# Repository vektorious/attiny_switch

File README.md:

# attiny_switch

Repository layout:
- `src/`: ATtiny1614 firmware (PlatformIO project)
- `pcb/`: KiCad project and gerbers

## Firmware target

- MCU: `ATtiny1614`
- `PA1`: ISP772T `IN` control
- `PA0`: dedicated `UPDI/RESET` pin, reserved for programming/debug and **not** used for switch control

Current behavior:
- On reset, drive `PA1` low immediately
- Then loop forever: OFF 50 min, ON 10 min
- MCU sleeps in `STANDBY` and wakes from RTC once per minute

## PlatformIO

`platformio.ini` is configured for bare-metal register-level C (no Arduino framework).

Build:

```powershell
pio run
```

Upload over UPDI (PA0):

1. Set your serial port in `platformio.ini` (`upload_port = COMx`).
2. Run:

```powershell
pio run -t upload
```

The configured upload command uses `avrdude` with `serialupdi`.

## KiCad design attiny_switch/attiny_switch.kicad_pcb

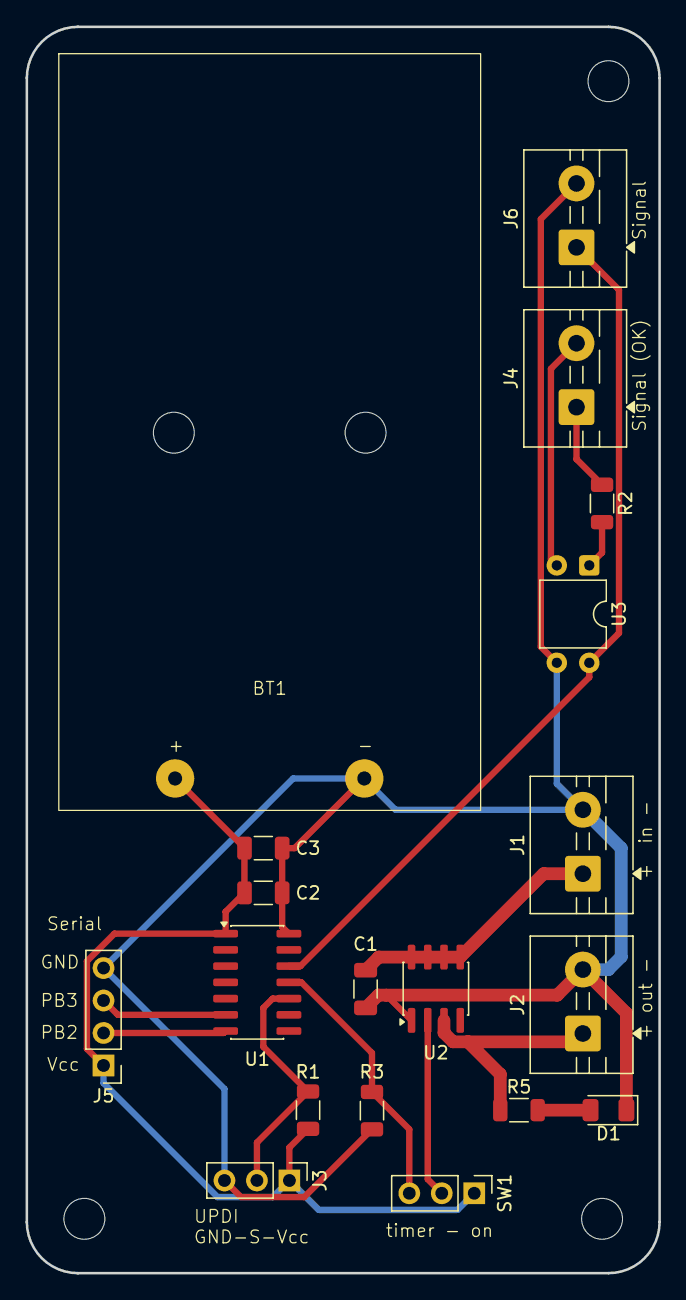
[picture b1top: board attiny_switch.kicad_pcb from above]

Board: 2 copper layers, 49.5 x 97.5 mm, 22 parts (0 on the bottom side), 14 nets.

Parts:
BT1: Battery_Cell; Untitled
C1, C2: 100nF; C_1206_3216Metric
C3: 10uF; C_1206_3216Metric
D1: LED; LED_1206_3216Metric
H1, H2, H3: MountingHole; MountingHole_3.2mm_M3
J1: 12V in; TerminalBlock_MaiXu_MX126-5.0-02P_1x02_P5.00mm
J2: 12V out; TerminalBlock_MaiXu_MX126-5.0-02P_1x02_P5.00mm
J3: UPDI Connector; PinHeader_1x03_P2.54mm_Vertical
J4: RPI Signal (OK); TerminalBlock_MaiXu_MX126-5.0-02P_1x02_P5.00mm
J5: Serial Connector; PinHeader_1x04_P2.54mm_Vertical
J6: RPI Signal; TerminalBlock_MaiXu_MX126-5.0-02P_1x02_P5.00mm
R1: 4,7k; R_1206_3216Metric
R2: 1k87; R_1206_3216Metric
R3: 100k; R_1206_3216Metric
R5: 7,5k; R_1206_3216Metric
SW1: SW_DPDT_x2; PinHeader_1x03_P2.54mm_Vertical
U1: ATtiny1614-SS; SOIC-14_3.9x8.7mm_P1.27mm
U2: ISP772T; SOIC-8_3.9x4.9mm_P1.27mm
U3: Optocoupler; DIP-4_W7.62mm

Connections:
GND: BT1.2 (-), C1.2, C2.1, C3.2, D1.1 (K), J1.2, J2.2, J3.3, J5.4, J6.2, R3.1, U1.14 (GND), U2.1 (GND), U3.3
unnamed: BT1.1 (+), C2.2, C3.1, J3.1, J5.1, R1.1, SW1.1 (A), U1.1 (VCC)
unnamed: D1.2 (A), R5.2
unnamed: C1.1, J1.1, U2.5 (VBB_1), U2.6 (VBB_2), U2.7 (VBB_3), U2.8 (VBB_4)
unnamed: J2.1, R5.1, U2.3 (OUT)
unnamed: J3.2, R1.2, U1.10 (~RESET/PA0)
unnamed: J4.1, R2.1
unnamed: J4.2, U3.2
unnamed: J5.2, U1.7 (PB2)
unnamed: J5.3, U1.6 (PB3)
unnamed: J6.1, U1.12 (PA2), U3.4
unnamed: R2.2, U3.1
unnamed: SW1.2 (B), U2.2 (IN)
unnamed: R3.2, SW1.3 (C), U1.11 (PA1)

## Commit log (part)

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2026-03-08 PCB rev1
2026-03-09 added code
2026-05-03 Save local changes before system wipe
